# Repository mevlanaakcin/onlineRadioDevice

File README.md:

# onlineRadioStreamDevice
Bir IoT projesi olarak internet tabanlı radio yayın akışı oynatma projesi<br>
<h3>PCB Tasarımı</h3><br>
Elektronik devre şeması ve PCB board tasarımı Eagle de tasarlandı.<br>

<h3>Masaüstü Uygulama</h3><br>
C# ile masaüstü uygulaması sayesinde cihazın set ayarları yapılabiliyor. Wifi bilgileri set edilebiliyor. Yayın akışı takip edilecek link bilgileri set edilebiliyor. Cihaza isim atanabiliyor. Tüm bu işlemler masaüstü uygulaması ile cihaz arasında serial haberleşme ile yapılıyor. Cihaza daha önceden set edilen bilgiler çekilebiliyor.<br>

<h3>Gömülü Yazılım</h3><br>
ESP8266 kullanarak Wifi desteğinden faydalanarak gömülü yazılımı geliştirdim.<br>
EEPROM hafıza kullanıldı.<br>
Serial Haberleşme kullanıldı.<br>
WPS Bağlantı kullanıldı.<br>
I2S kullanıldı.<br>

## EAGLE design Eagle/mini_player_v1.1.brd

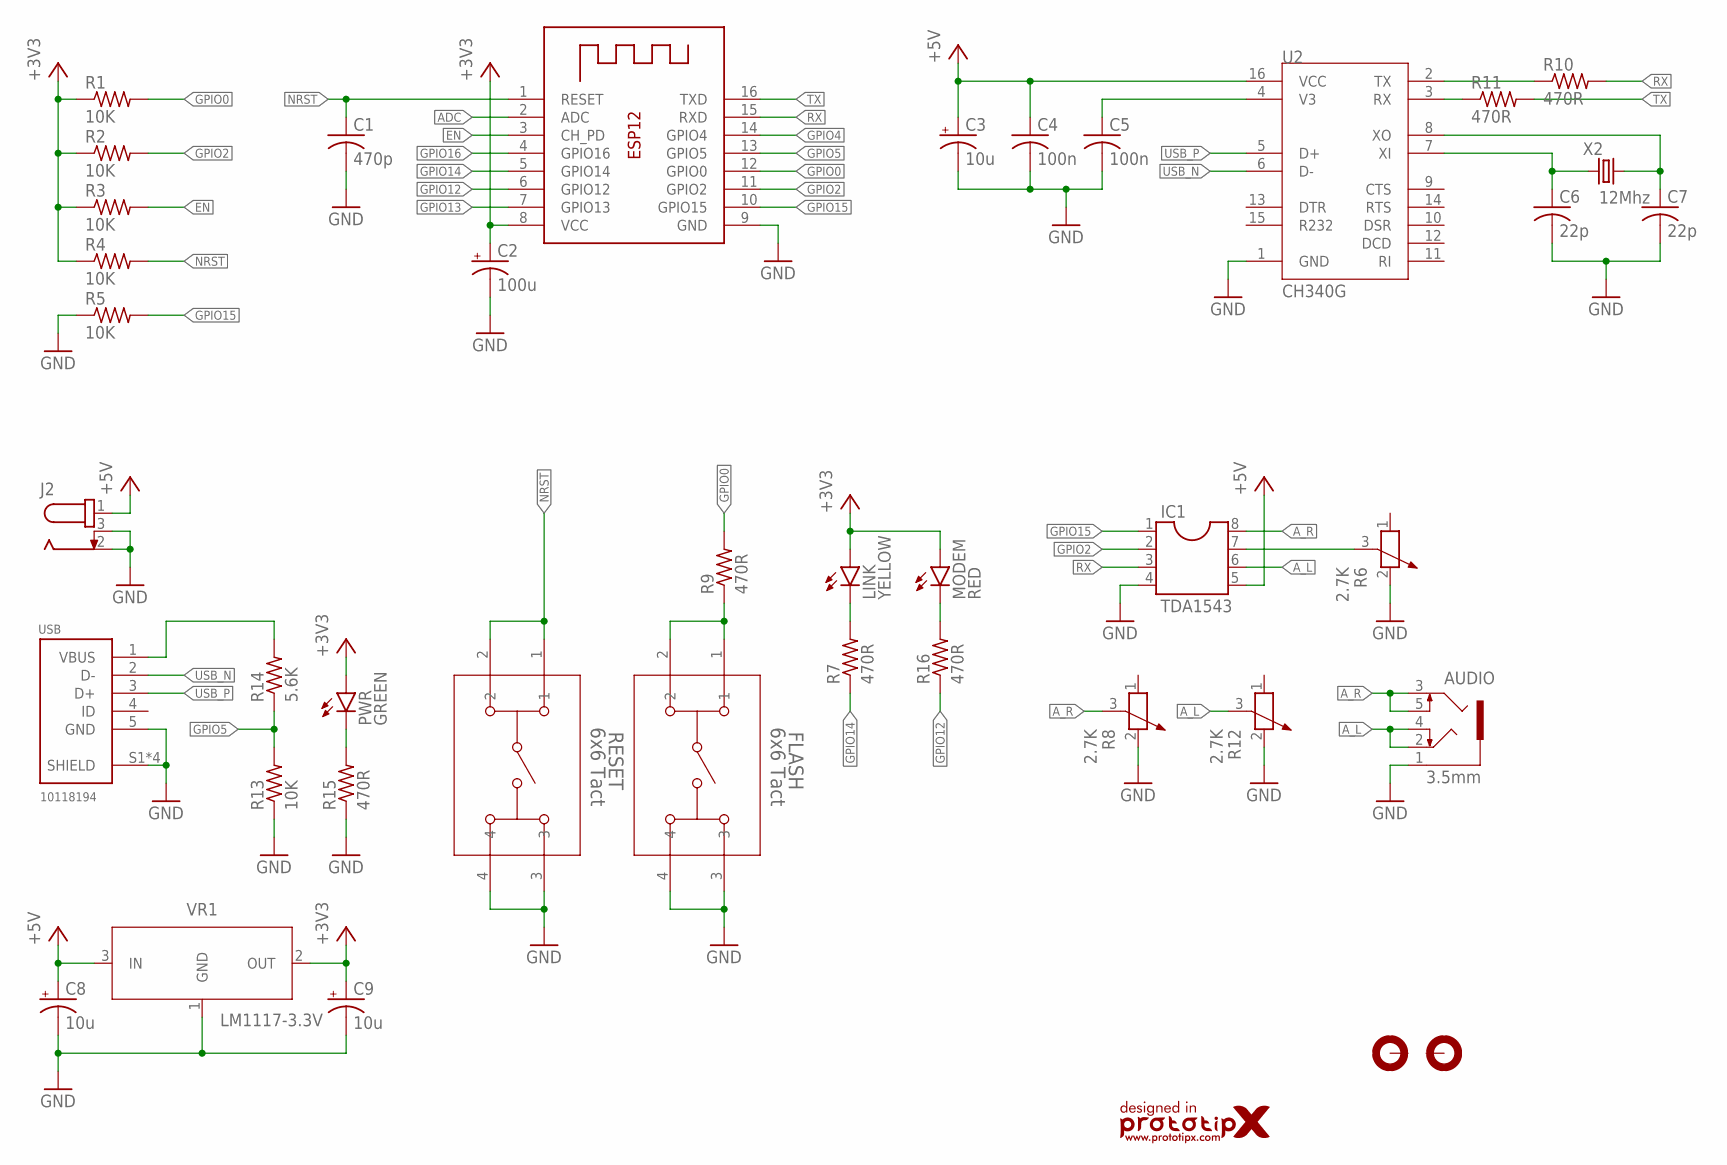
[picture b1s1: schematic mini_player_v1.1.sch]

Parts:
AUDIO: 3.5mm; 1503_09
C1: 470p; C0805
C2: 100u; SMC_B
C3, C8, C9: 10u; SMC_B
C4, C5: 100n; C0805
C6, C7: 22p; C0805
FLASH: 6x6 Tact; SW4_1825910-G
H1, H2: MOUNT-PAD-ROUND3.6; 3,6-PAD
IC1: TDA1543; DIL08
J2: 694106301002
LINK: YELLOW; LED3MM
LOGO1: PROTOTIPXDESIGN2; PROTOTIPX_DESING_15MM
MODEM: RED; LED3MM
PWR: GREEN; LED3MM
R1, R2, R3, R4, R5, R13: 10K; R0805
R6, R8, R12: 2.7K; PT-10
R7, R9, R10, R11, R15, R16: 470R; R0805
R14: 5.6K; R0805
RESET: 6x6 Tact; SW4_1825910-G
U1: ESP12E; ESP-12
U2: CH340G; SOIC16
USB: 10118194
VR1: LM1117-3.3V; SOT230P700X170-4
X2: 12Mhz; 5032/2P

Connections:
+3V3: C2.+, C9.+, LINK.A, MODEM.A, PWR.A, R1.1, R2.1, R3.1, R4.1, U1.8 (VCC), VR1.2 (OUT)
+5V: C3.+, C4.1, C8.+, IC1.5, J2.1, U2.16 (VCC), VR1.3 (IN)
ADC: U1.2 (ADC)
A_L: AUDIO.2, AUDIO.4, IC1.6, R12.3
A_R: AUDIO.3, AUDIO.5, IC1.8, R8.3
EN: R3.2, U1.3 (CH_PD)
GND: AUDIO.1, C1.2, C2.-, C3.-, C4.2, C5.2, C6.2, C7.2, C8.-, C9.-, FLASH.3, FLASH.4, IC1.4, J2.2, J2.3, R5.1, R6.2, R8.2, R12.2, R13.1, R15.1, RESET.3, RESET.4, U1.9 (GND), U2.1 (GND), USB.5 (GND), USB.S1 (SHIELD), USB.S2 (SHIELD), USB.S3 (SHIELD), USB.S6 (SHIELD), VR1.1 (GND)
GPIO0: R1.2, R9.2, U1.12 (GPIO0)
GPIO2: IC1.2, R2.2, U1.11 (GPIO2)
GPIO4: U1.14 (GPIO4)
GPIO5: R13.2, R14.1, U1.13 (GPIO5)
GPIO12: R16.1, U1.6 (GPIO12)
GPIO13: U1.7 (GPIO13)
GPIO14: R7.1, U1.5 (GPIO14)
GPIO15: IC1.1, R5.2, U1.10 (GPIO15)
GPIO16: U1.4 (GPIO16)
unnamed: R14.2, USB.1 (VBUS)
unnamed: FLASH.1, FLASH.2, R9.1
unnamed: C5.1, U2.4 (V3)
unnamed: C6.1, U2.7 (XI), X2.1
unnamed: C7.1, U2.8 (XO), X2.2
unnamed: R11.1, U2.3 (RX)
unnamed: R10.1, U2.2 (TX)
unnamed: MODEM.K (C), R16.2
unnamed: PWR.K (C), R15.2
unnamed: LINK.K (C), R7.2
NRST: C1.1, R4.2, RESET.1, RESET.2, U1.1 (RESET)
RX: IC1.3, R10.2, U1.15 (RXD)
TX: R11.2, U1.16 (TXD)
USB_N: U2.6 (D-), USB.2 (D-)
USB_P: U2.5 (D+), USB.3 (D+)
VREF: IC1.7, R6.3

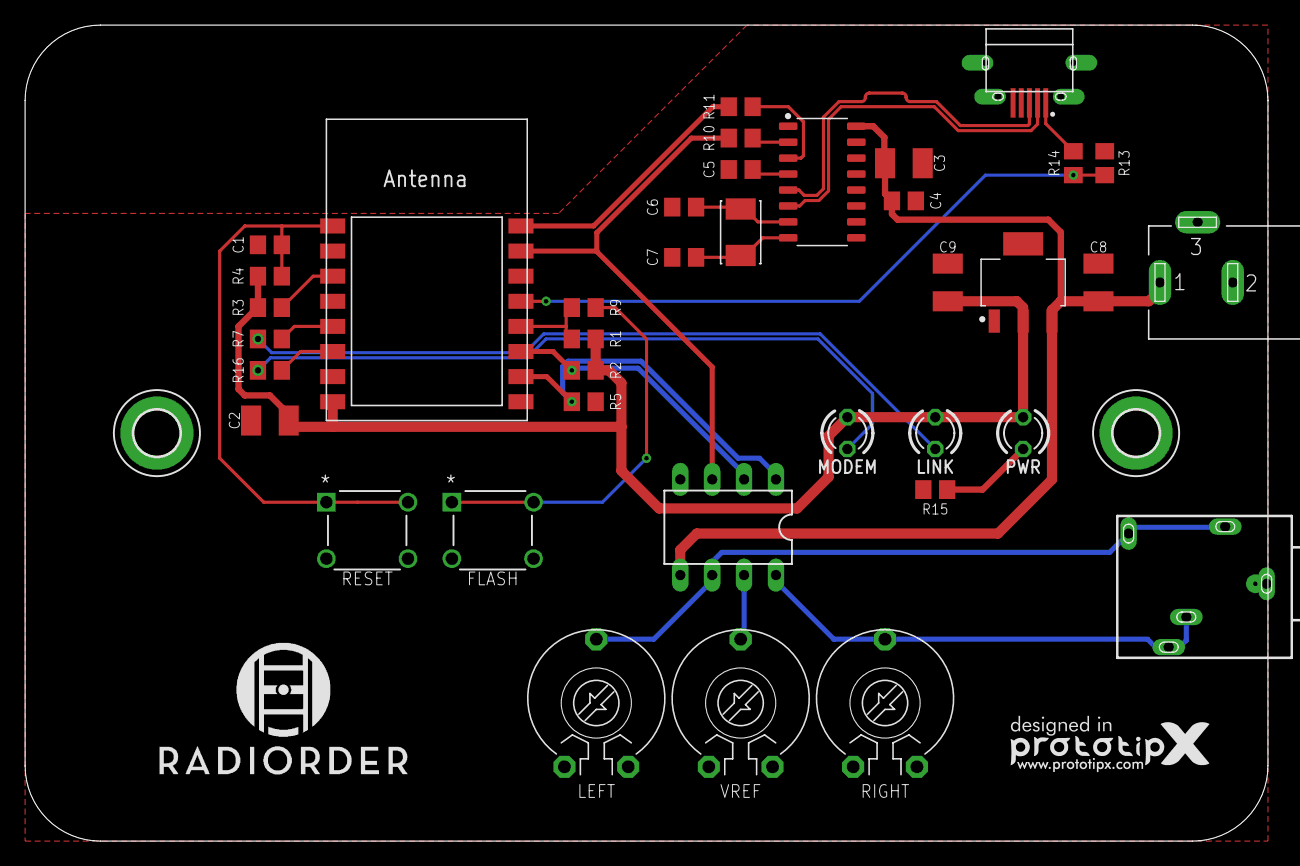
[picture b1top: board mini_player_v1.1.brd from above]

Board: 2 copper layers, 99.3 x 65.0 mm, 41 parts (0 on the bottom side), 28 nets.

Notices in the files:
parts and their libraries:
COPYRIGHT: Copyright (C) 2016 Accelerated Designs. All rights reserved
